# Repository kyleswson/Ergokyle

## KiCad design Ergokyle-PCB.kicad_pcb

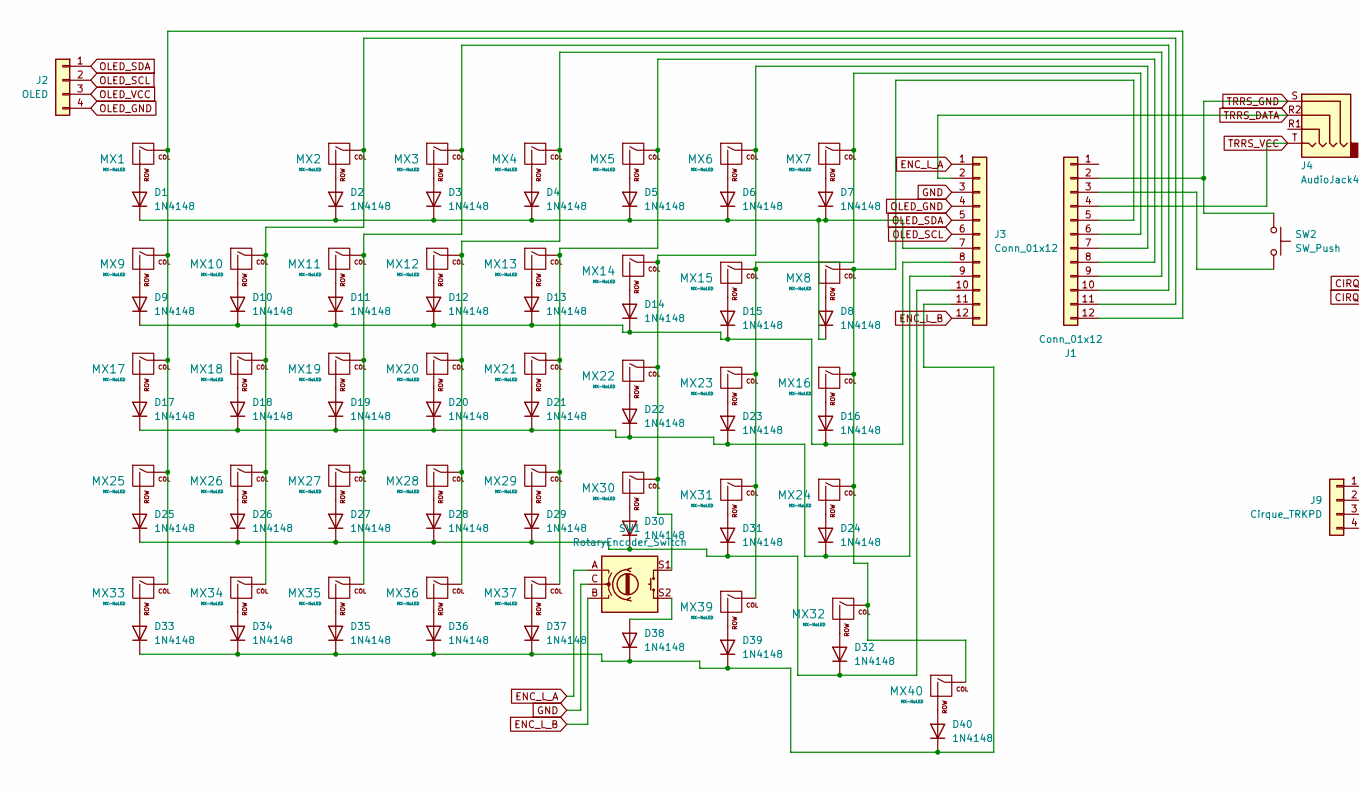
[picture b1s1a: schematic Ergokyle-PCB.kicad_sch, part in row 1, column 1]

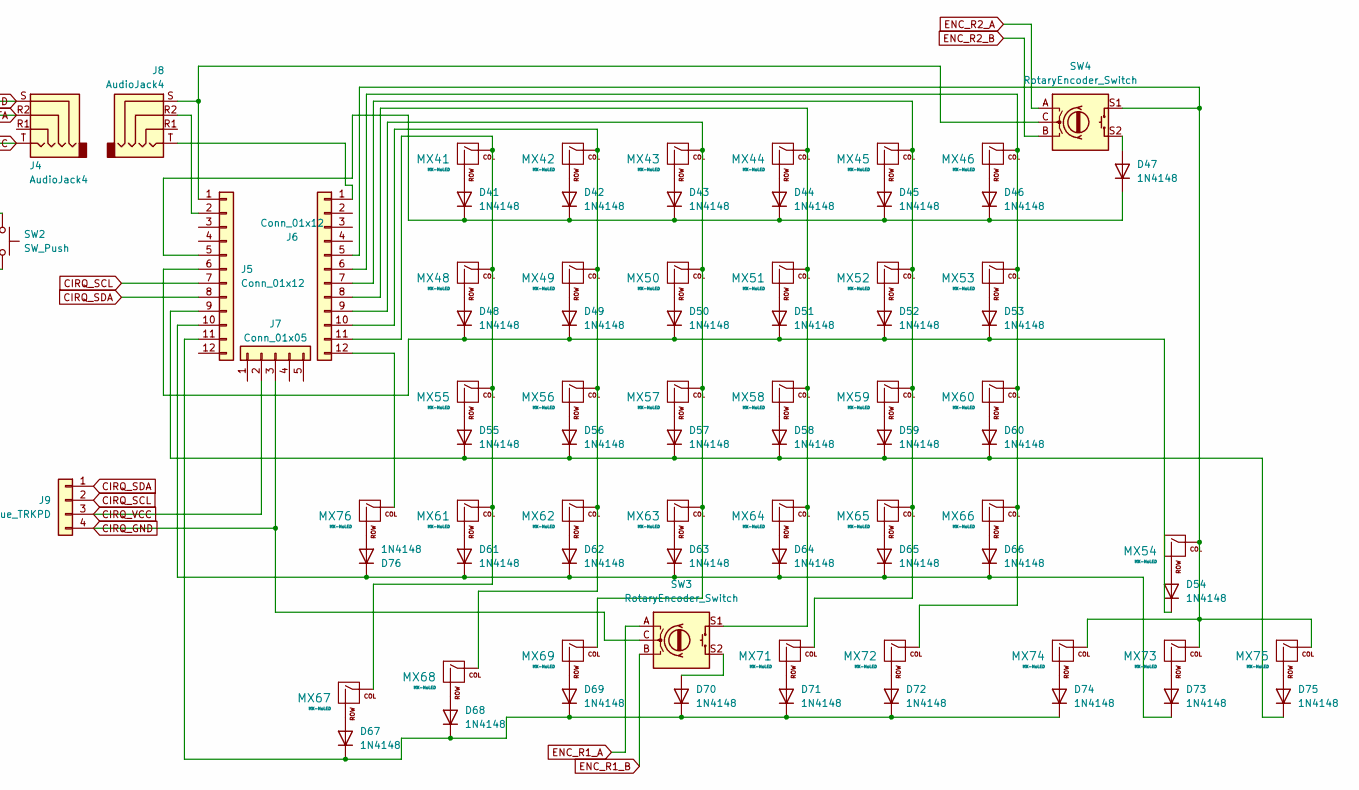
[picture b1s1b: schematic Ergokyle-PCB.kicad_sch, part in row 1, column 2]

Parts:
D1, D2, D3, D4, D5, D6, D7, D8, D9, D10, D11, D12, D13, D14, D15, D16, D17, D18, D19, D20, D21, D22, D23, D24, D25, D26, D27, D28, D29, D30, D31, D32, D33, D34, D35, D36, D37, D38, D39, D40, D41, D42, D43, D44, D45, D46, D47, D48, D49, D50, D51, D52, D53, D54, D55, D56, D57, D58, D59, D60, D61, D62, D63, D64, D65, D66, D67, D68, D69, D70, D71, D72, D73, D74, D75, D76: 1N4148; D_DO-35_SOD27_P7.62mm_Horizontal
J1, J3, J5, J6: Conn_01x12; PinSocket_1x12_P2.54mm_Vertical
J2: OLED; PinSocket_1x04_P2.54mm_Vertical
J4, J8: AudioJack4; Jack_3.5mm_PJ320E_Horizontal
J7: Conn_01x05; PinSocket_1x05_P2.54mm_Vertical
J9: Cirque_TRKPD; PinSocket_1x04_P2.54mm_Vertical
MX1, MX2, MX3, MX4, MX5, MX6, MX7, MX8, MX9, MX10, MX11, MX12, MX13, MX14, MX15, MX16, MX17, MX18, MX19, MX20, MX21, MX22, MX23, MX24, MX25, MX26, MX27, MX28, MX29, MX30, MX31, MX32, MX33, MX34, MX35, MX36, MX37, MX39, MX41, MX42, MX43, MX44, MX45, MX46, MX48, MX49, MX50, MX51, MX52, MX53, MX54, MX55, MX56, MX57, MX58, MX59, MX60, MX61, MX62, MX63, MX64, MX65, MX66, MX68, MX69, MX71, MX72, MX73, MX74, MX75, MX76: MX-NoLED; SW_MX_HS_CPG151101S11_1u
MX40, MX67: MX-NoLED; SW_MX_HS_CPG151101S11_1.25u
SW1, SW3: RotaryEncoder_Switch; RollerEncoder_Panasonic_EVQWGD001
SW2: SW_Push; Kailh red micro switch silent
SW4: RotaryEncoder_Switch; RotaryEncoder_Alps_EC11E-Switch_Vertical_H20mm_MountingHoles

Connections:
CIRQ_GND: J7.3, J9.4, SW3.C
CIRQ_SCL: J5.7, J9.2
CIRQ_SDA: J5.8, J9.1
CIRQ_VCC: J7.2, J9.3
ENC_L_A: J3.1, SW1.A
ENC_L_B: J3.12, SW1.B
ENC_R1_A: SW3.A
ENC_R1_B: SW3.B
ENC_R2_A: SW4.A
ENC_R2_B: SW4.B
GND: J3.3, SW1.C
unnamed: D1.2 (A), MX1.2 (ROW)
unnamed: D1.1 (K), D2.1 (K), D3.1 (K), D4.1 (K), D5.1 (K), D6.1 (K), D7.1 (K), D8.1 (K), J3.7
unnamed: D2.2 (A), MX2.2 (ROW)
unnamed: D3.2 (A), MX3.2 (ROW)
unnamed: D4.2 (A), MX4.2 (ROW)
unnamed: D5.2 (A), MX5.2 (ROW)
unnamed: D6.2 (A), MX6.2 (ROW)
unnamed: D7.2 (A), MX7.2 (ROW)
unnamed: D8.2 (A), MX8.2 (ROW)
unnamed: D9.2 (A), MX9.2 (ROW)
unnamed: D10.2 (A), MX10.2 (ROW)
unnamed: D9.1 (K), D10.1 (K), D11.1 (K), D12.1 (K), D13.1 (K), D14.1 (K), D15.1 (K), D16.1 (K), J3.8
unnamed: D11.2 (A), MX11.2 (ROW)
unnamed: D12.2 (A), MX12.2 (ROW)
unnamed: D13.2 (A), MX13.2 (ROW)
unnamed: D14.2 (A), MX14.2 (ROW)
unnamed: D15.2 (A), MX15.2 (ROW)
unnamed: D16.2 (A), MX16.2 (ROW)
unnamed: D17.2 (A), MX17.2 (ROW)
unnamed: D17.1 (K), D18.1 (K), D19.1 (K), D20.1 (K), D21.1 (K), D22.1 (K), D23.1 (K), D24.1 (K), J3.9
unnamed: D18.2 (A), MX18.2 (ROW)
unnamed: D19.2 (A), MX19.2 (ROW)
unnamed: D20.2 (A), MX20.2 (ROW)
unnamed: D21.2 (A), MX21.2 (ROW)
unnamed: D22.2 (A), MX22.2 (ROW)
unnamed: D23.2 (A), MX23.2 (ROW)
unnamed: D24.2 (A), MX24.2 (ROW)
unnamed: D25.2 (A), MX25.2 (ROW)
unnamed: D25.1 (K), D26.1 (K), D27.1 (K), D28.1 (K), D29.1 (K), D30.1 (K), D31.1 (K), D32.1 (K), J3.10
unnamed: D26.2 (A), MX26.2 (ROW)
unnamed: D27.2 (A), MX27.2 (ROW)
unnamed: D28.2 (A), MX28.2 (ROW)
unnamed: D29.2 (A), MX29.2 (ROW)
unnamed: D30.2 (A), MX30.2 (ROW)
unnamed: D31.2 (A), MX31.2 (ROW)
unnamed: D32.2 (A), MX32.2 (ROW)
unnamed: D33.2 (A), MX33.2 (ROW)
unnamed: D33.1 (K), D34.1 (K), D35.1 (K), D36.1 (K), D37.1 (K), D38.1 (K), D39.1 (K), D40.1 (K), J3.11
unnamed: D34.2 (A), MX34.2 (ROW)
unnamed: D35.2 (A), MX35.2 (ROW)
unnamed: D36.2 (A), MX36.2 (ROW)
unnamed: D37.2 (A), MX37.2 (ROW)
unnamed: D38.2 (A), SW1.S2
unnamed: D39.2 (A), MX39.2 (ROW)
unnamed: D40.2 (A), MX40.2 (ROW)
unnamed: D41.2 (A), MX41.2 (ROW)
unnamed: D41.1 (K), D42.1 (K), D43.1 (K), D44.1 (K), D45.1 (K), D46.1 (K), D47.1 (K), J5.5
unnamed: D42.2 (A), MX42.2 (ROW)
unnamed: D43.2 (A), MX43.2 (ROW)
unnamed: D44.2 (A), MX44.2 (ROW)
unnamed: D45.2 (A), MX45.2 (ROW)
unnamed: D46.2 (A), MX46.2 (ROW)
unnamed: D47.2 (A), SW4.S2
unnamed: D48.2 (A), MX48.2 (ROW)
unnamed: D48.1 (K), D49.1 (K), D50.1 (K), D51.1 (K), D52.1 (K), D53.1 (K), D54.1 (K), J5.6
unnamed: D49.2 (A), MX49.2 (ROW)
unnamed: D50.2 (A), MX50.2 (ROW)
unnamed: D51.2 (A), MX51.2 (ROW)
unnamed: D52.2 (A), MX52.2 (ROW)
unnamed: D53.2 (A), MX53.2 (ROW)
unnamed: D54.2 (A), MX54.2 (ROW)
unnamed: D55.2 (A), MX55.2 (ROW)
unnamed: D55.1 (K), D56.1 (K), D57.1 (K), D58.1 (K), D59.1 (K), D60.1 (K), D75.1 (K), J5.9
unnamed: D56.2 (A), MX56.2 (ROW)
unnamed: D57.2 (A), MX57.2 (ROW)
unnamed: D58.2 (A), MX58.2 (ROW)
unnamed: D59.2 (A), MX59.2 (ROW)
unnamed: D60.2 (A), MX60.2 (ROW)
unnamed: D61.2 (A), MX61.2 (ROW)
unnamed: D61.1 (K), D62.1 (K), D63.1 (K), D64.1 (K), D65.1 (K), D66.1 (K), D73.1 (K), D76.1 (K), J5.10
unnamed: D62.2 (A), MX62.2 (ROW)
unnamed: D63.2 (A), MX63.2 (ROW)
unnamed: D64.2 (A), MX64.2 (ROW)
unnamed: D65.2 (A), MX65.2 (ROW)
unnamed: D66.2 (A), MX66.2 (ROW)
unnamed: D67.2 (A), MX67.2 (ROW)
unnamed: D67.1 (K), D68.1 (K), D69.1 (K), D70.1 (K), D71.1 (K), D72.1 (K), D74.1 (K), J5.11
unnamed: D68.2 (A), MX68.2 (ROW)
unnamed: D69.2 (A), MX69.2 (ROW)
unnamed: D70.2 (A), SW3.S2
unnamed: D71.2 (A), MX71.2 (ROW)
unnamed: D72.2 (A), MX72.2 (ROW)
unnamed: D73.2 (A), MX73.2 (ROW)
unnamed: D74.2 (A), MX74.2 (ROW)
unnamed: D75.2 (A), MX75.2 (ROW)
unnamed: D76.2 (A), MX76.2 (ROW)
unnamed: J1.3, SW2.2
unnamed: J1.5, MX8.1 (COL), MX16.1 (COL), MX24.1 (COL), MX32.1 (COL), MX40.1 (COL)
unnamed: J1.6, MX7.1 (COL), MX15.1 (COL), MX23.1 (COL), MX31.1 (COL), MX39.1 (COL)
unnamed: J1.7, MX6.1 (COL), MX14.1 (COL), MX22.1 (COL), MX30.1 (COL), SW1.S1
unnamed: J1.8, MX5.1 (COL), MX13.1 (COL), MX21.1 (COL), MX29.1 (COL), MX37.1 (COL)
unnamed: J1.9, MX4.1 (COL), MX12.1 (COL), MX20.1 (COL), MX28.1 (COL), MX36.1 (COL)
unnamed: J1.10, MX3.1 (COL), MX11.1 (COL), MX19.1 (COL), MX27.1 (COL), MX35.1 (COL)
unnamed: J1.11, MX2.1 (COL), MX10.1 (COL), MX18.1 (COL), MX26.1 (COL), MX34.1 (COL)
unnamed: J1.12, MX1.1 (COL), MX9.1 (COL), MX17.1 (COL), MX25.1 (COL), MX33.1 (COL)
unnamed: J5.1, J8.S, SW4.C
unnamed: J5.2, J8.R2
unnamed: J6.1, J8.T
unnamed: J6.5, MX54.1 (COL), MX73.1 (COL), MX74.1 (COL), MX75.1 (COL), SW4.S1
unnamed: J6.6, MX46.1 (COL), MX53.1 (COL), MX60.1 (COL), MX66.1 (COL), MX72.1 (COL)
unnamed: J6.7, MX45.1 (COL), MX52.1 (COL), MX59.1 (COL), MX65.1 (COL), MX71.1 (COL)
unnamed: J6.8, MX44.1 (COL), MX51.1 (COL), MX58.1 (COL), MX64.1 (COL), SW3.S1
unnamed: J6.9, MX43.1 (COL), MX50.1 (COL), MX57.1 (COL), MX63.1 (COL), MX69.1 (COL)
unnamed: J6.10, MX42.1 (COL), MX49.1 (COL), MX56.1 (COL), MX62.1 (COL), MX68.1 (COL)
unnamed: J6.11, MX41.1 (COL), MX48.1 (COL), MX55.1 (COL), MX61.1 (COL), MX67.1 (COL)
unnamed: J6.12, MX76.1 (COL)
OLED_GND: J2.4, J3.4
OLED_SCL: J2.2, J3.6
OLED_SDA: J2.1, J3.5
OLED_VCC: J2.3
TRRS_DATA: J3.2, J4.R2
TRRS_GND: J1.2, J4.S, SW2.1
TRRS_VCC: J1.4, J4.T

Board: 2 copper layers, 162 parts (1 on the bottom side), 119 nets, no tracks yet.

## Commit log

2025-02-19 Initialize
2025-02-19 Add footprint libraries
2025-02-21 PCB worked
2025-02-23 PCB file update
